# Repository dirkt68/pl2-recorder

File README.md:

#Automated Recorder Project
##Texas Tech University PL2

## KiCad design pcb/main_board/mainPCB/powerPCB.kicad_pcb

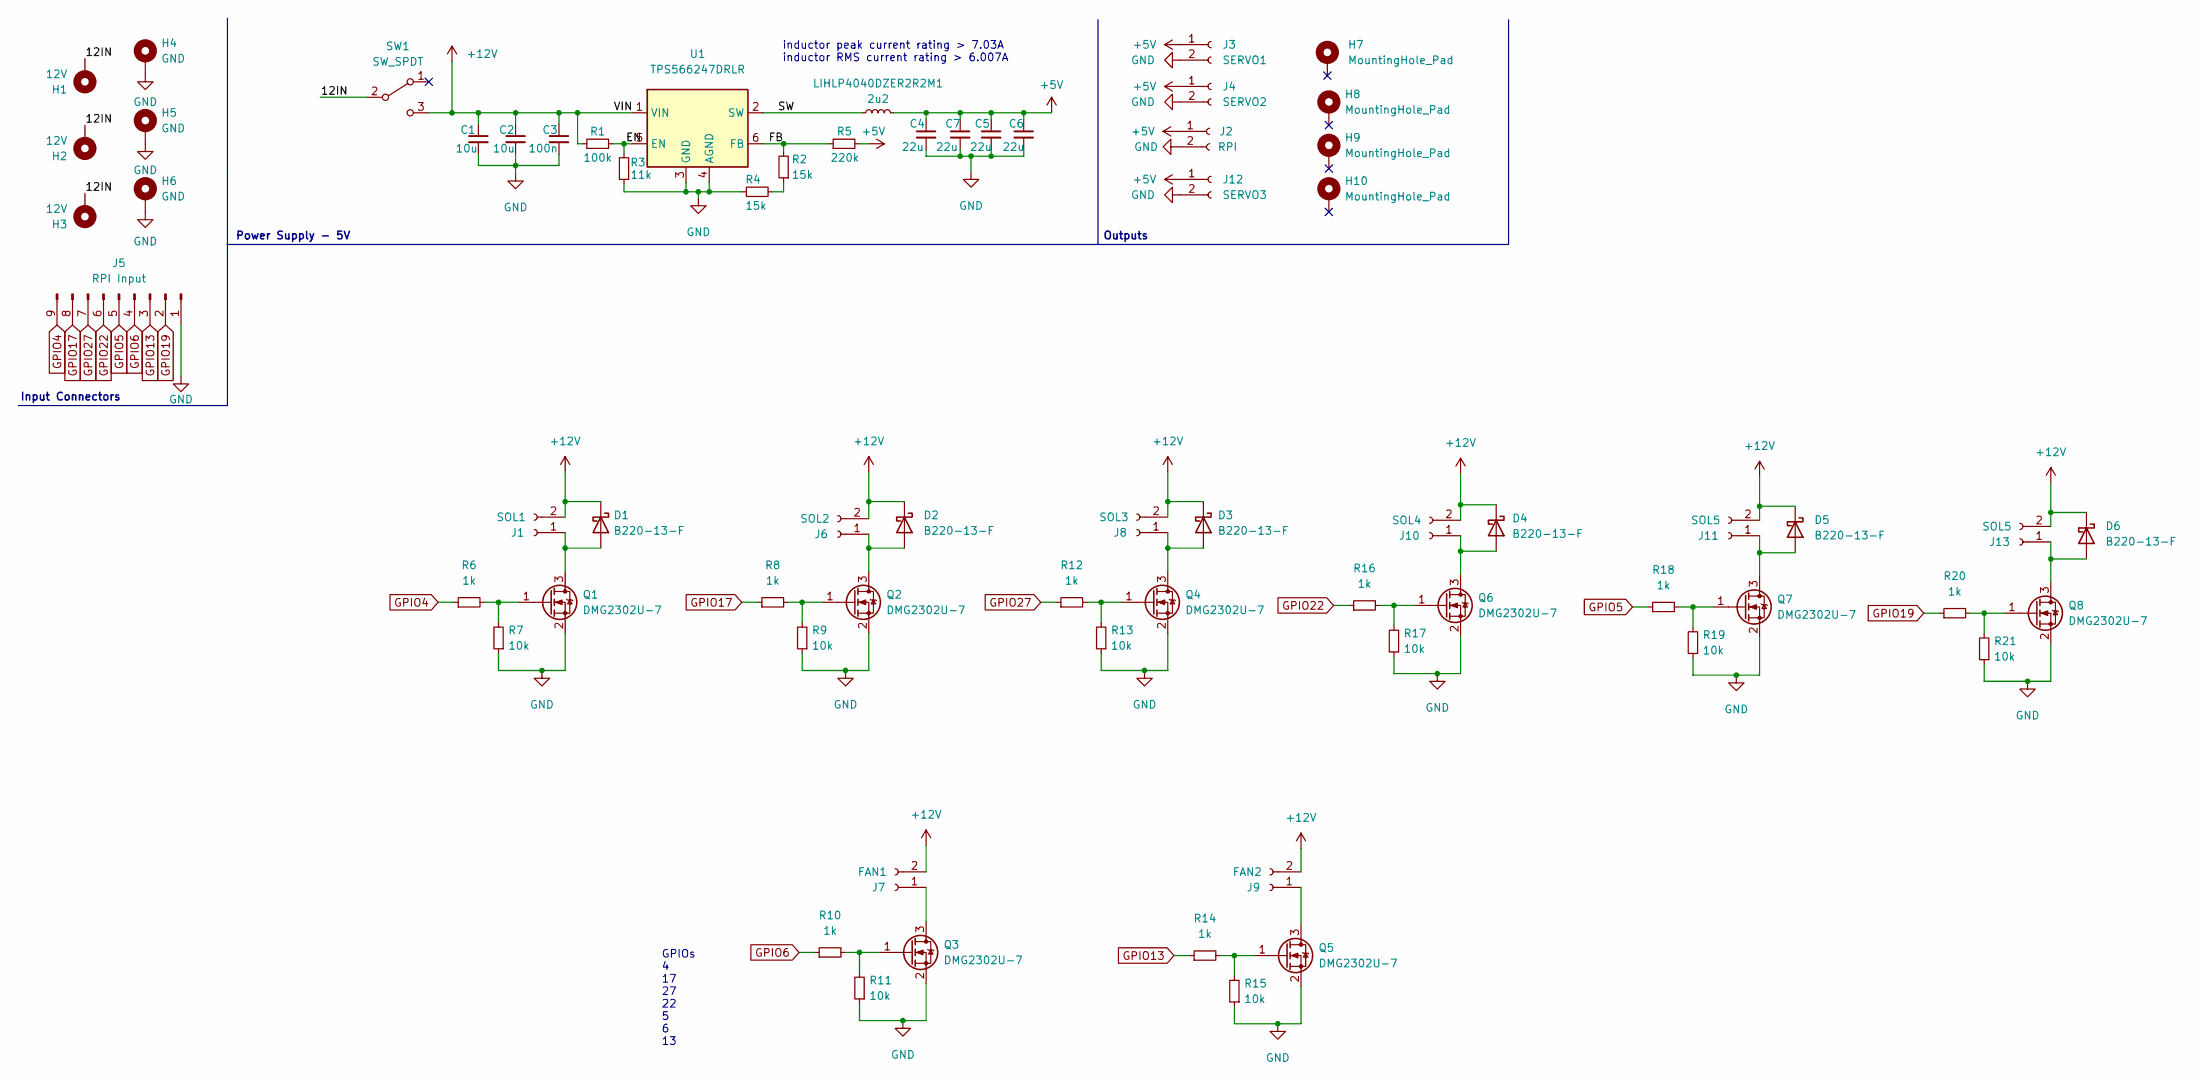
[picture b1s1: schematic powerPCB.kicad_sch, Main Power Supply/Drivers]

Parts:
C1, C2: 10u; C_1206_3216Metric
C3: 100n; C_0603_1608Metric
C4, C5, C6, C7: 22u; C_1210_3225Metric
D1, D2, D3, D4, D5, D6: B220-13-F; D_SMB
H1, H2, H3: 12V; MountingHole_2.2mm_M2_DIN965_Pad
H4, H5, H6: GND; MountingHole_2.2mm_M2_DIN965_Pad
H7, H8, H9, H10: MountingHole_Pad; MountingHole_3.2mm_M3_DIN965_Pad
J1: SOL1; PinHeader_1x02_P5.00mm
J2: RPI; PinHeader_1x02_P5.00mm
J3: SERVO1; PinHeader_1x02_P5.00mm
J4: SERVO2; PinHeader_1x02_P5.00mm
J5: RPI Input; PinHeader_1x09_P2.54mm_Vertical
J6: SOL2; PinHeader_1x02_P5.00mm
J7: FAN1; PinHeader_1x02_P5.00mm
J8: SOL3; PinHeader_1x02_P5.00mm
J9: FAN2; PinHeader_1x02_P5.00mm
J10: SOL4; PinHeader_1x02_P5.00mm
J11, J13: SOL5; PinHeader_1x02_P5.00mm
J12: SERVO3; PinHeader_1x02_P5.00mm
LIHLP4040DZER2R2M1: 2u2; L_Vishay_IHLP-4040
Q1, Q2, Q3, Q4, Q5, Q6, Q7, Q8: DMG2302U-7; SOT-23
R1: 100k; R_0603_1608Metric
R2, R4: 15k; R_0603_1608Metric
R3: 11k; R_0603_1608Metric
R5: 220k; R_1206_3216Metric
R6, R8, R10, R12, R14, R16, R18, R20: 1k; R_0805_2012Metric
R7, R9, R11, R13, R15, R17, R19, R21: 10k; R_0805_2012Metric
SW1: SW_SPDT; remote switch
U1: TPS566247DRLR; SOT-563

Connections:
+5V: C4.1, C5.1, C6.1, C7.1, J2.1, J3.1, J4.1, J12.1, LIHLP4040DZER2R2M1.2, R5.2
+12V: C1.1, C2.1, C3.1, D1.1 (K), D2.1 (K), D3.1 (K), D4.1 (K), D5.1 (K), D6.1 (K), J1.2, J6.2, J7.2, J8.2, J9.2, J10.2, J11.2, J13.2, R1.1, SW1.3 (C), U1.1 (VIN)
/12IN: H1.1, H2.1, H3.1, SW1.2 (B)
/EN: R1.2, R3.2, U1.5 (EN)
/FB: R2.2, R5.1, U1.6 (FB)
/SW: LIHLP4040DZER2R2M1.1, U1.2 (SW)
GND: C1.2, C2.2, C3.2, C4.2, C5.2, C6.2, C7.2, H4.1, H5.1, H6.1, J2.2, J3.2, J4.2, J5.1, J12.2, Q1.2 (S), Q2.2 (S), Q3.2 (S), Q4.2 (S), Q5.2 (S), Q6.2 (S), Q7.2 (S), Q8.2 (S), R3.1, R4.1, R7.1, R9.1, R11.1, R13.1, R15.1, R17.1, R19.1, R21.1, U1.3 (GND), U1.4 (AGND)
GPIO4: J5.9, R6.1
GPIO5: J5.5, R18.1
GPIO6: J5.4, R10.1
GPIO13: J5.3, R14.1
GPIO17: J5.8, R8.1
GPIO19: J5.2, R20.1
GPIO22: J5.6, R16.1
GPIO27: J5.7, R12.1
unnamed: D1.2 (A), J1.1, Q1.3 (D)
unnamed: D2.2 (A), J6.1, Q2.3 (D)
unnamed: D3.2 (A), J8.1, Q4.3 (D)
unnamed: D5.2 (A), J11.1, Q7.3 (D)
unnamed: D6.2 (A), J13.1, Q8.3 (D)
unnamed: J7.1, Q3.3 (D)
unnamed: J9.1, Q5.3 (D)
unnamed: Q1.1 (G), R6.2, R7.2
unnamed: Q2.1 (G), R8.2, R9.2
unnamed: Q3.1 (G), R10.2, R11.2
unnamed: Q4.1 (G), R12.2, R13.2
unnamed: Q5.1 (G), R14.2, R15.2
unnamed: Q6.1 (G), R16.2, R17.2
unnamed: D4.2 (A), J10.1, Q6.3 (D)
unnamed: Q7.1 (G), R18.2, R19.2
unnamed: Q8.1 (G), R20.2, R21.2
unnamed: R2.1, R4.2

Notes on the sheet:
Power Supply - 5V
Input Connectors
Outputs
inductor peak current rating > 7.03A inductor RMS current rating > 6.007A
GPIOs 4 17 27 22 5 6 13

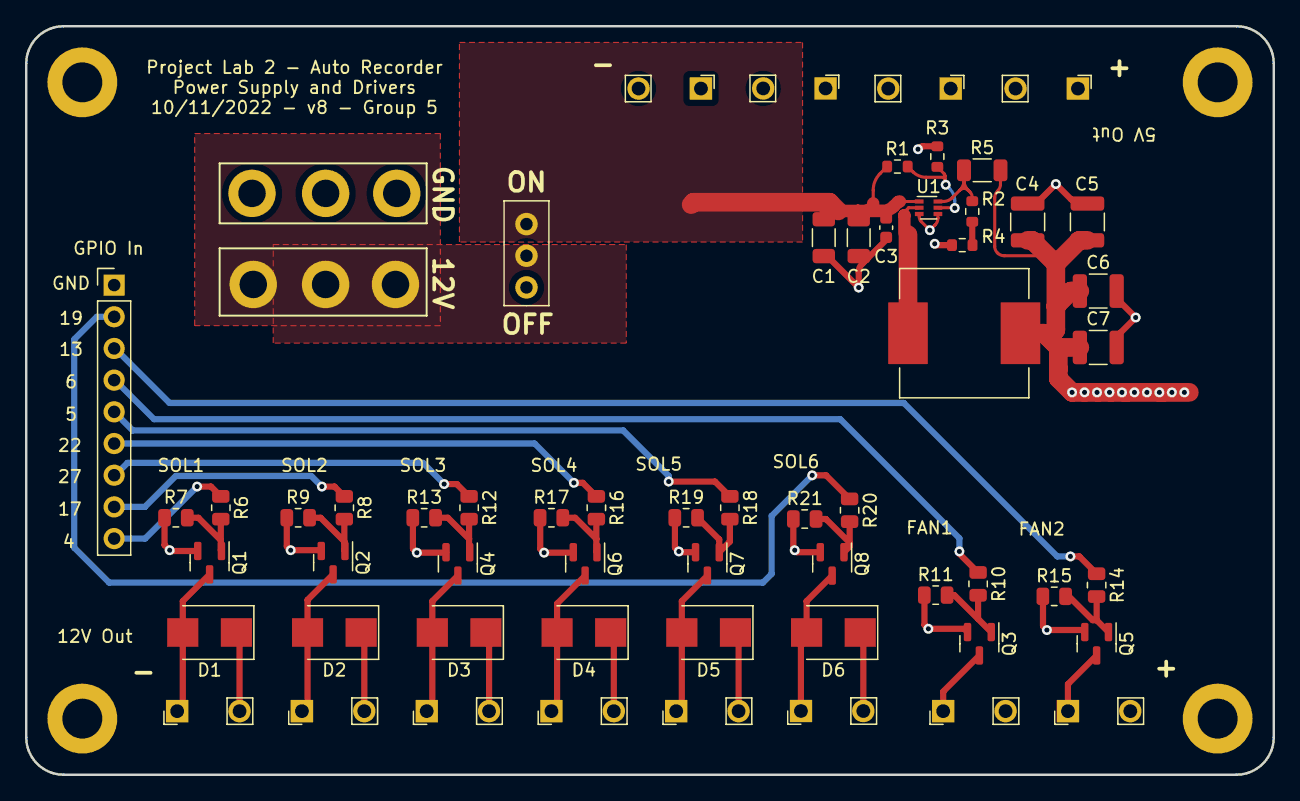
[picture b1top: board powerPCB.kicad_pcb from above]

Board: 4 copper layers, 100.0 x 60.0 mm, 68 parts (0 on the bottom side), 32 nets.

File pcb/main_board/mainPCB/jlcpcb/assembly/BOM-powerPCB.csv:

Comment,Designator,Footprint,LCSC
100k,R1,R_0603_1608Metric,
GND,H5,MountingHole_2.2mm_M2_DIN965_Pad,
22u,C5,C_1210_3225Metric,
SOL4,J10,PinHeader_1x02_P5.00mm,
SERVO1,J3,PinHeader_1x02_P5.00mm,
11k,R3,R_0603_1608Metric,
15k,R2,R_0603_1608Metric,
FAN1,J7,PinHeader_1x02_P5.00mm,
10u,C2,C_1206_3216Metric,
SOL2,J6,PinHeader_1x02_P5.00mm,
FAN2,J9,PinHeader_1x02_P5.00mm,
GND,H6,MountingHole_2.2mm_M2_DIN965_Pad,
SERVO2,J4,PinHeader_1x02_P5.00mm,
SOL3,J8,PinHeader_1x02_P5.00mm,
22u,C4,C_1210_3225Metric,
12V,H2,MountingHole_2.2mm_M2_DIN965_Pad,
100n,C3,C_0603_1608Metric,
SOL1,J1,PinHeader_1x02_P5.00mm,
12V,H3,MountingHole_2.2mm_M2_DIN965_Pad,
RPI Input,J5,PinHeader_1x09_P2.54mm_Vertical,
12V,H1,MountingHole_2.2mm_M2_DIN965_Pad,
SW_SPDT,SW1,remote switch,
10u,C1,C_1206_3216Metric,
TPS566247DRLR,U1,SOT-563,
22u,C6,C_1210_3225Metric,
220k,R5,R_1206_3216Metric,
GND,H4,MountingHole_2.2mm_M2_DIN965_Pad,
22u,C7,C_1210_3225Metric,
RPI,J2,PinHeader_1x02_P5.00mm,
15k,R4,R_0603_1608Metric,
SOL5,J11,PinHeader_1x02_P5.00mm,
10k,R19,R_0805_2012Metric,
1k,R18,R_0805_2012Metric,
10k,R17,R_0805_2012Metric,
1k,R16,R_0805_2012Metric,
10k,R15,R_0805_2012Metric,
1k,R14,R_0805_2012Metric,
10k,R13,R_0805_2012Metric,
1k,R12,R_0805_2012Metric,
10k,R11,R_0805_2012Metric,
1k,R10,R_0805_2012Metric,
10k,R9,R_0805_2012Metric,
1k,R8,R_0805_2012Metric,
10k,R7,R_0805_2012Metric,
1k,R6,R_0805_2012Metric,
DMG2302U-7,Q7,SOT-23,
DMG2302U-7,Q6,SOT-23,
DMG2302U-7,Q5,SOT-23,
DMG2302U-7,Q4,SOT-23,
DMG2302U-7,Q3,SOT-23,
DMG2302U-7,Q2,SOT-23,
DMG2302U-7,Q1,SOT-23,
B220-13-F,D5,D_SMB,
B220-13-F,D4,D_SMB,
B220-13-F,D3,D_SMB,
B220-13-F,D2,D_SMB,
B220-13-F,D1,D_SMB,
MountingHole_Pad,H9,MountingHole_3.2mm_M3_DIN965_Pad,
MountingHole_Pad,H10,MountingHole_3.2mm_M3_DIN965_Pad,
MountingHole_Pad,H8,MountingHole_3.2mm_M3_DIN965_Pad,
MountingHole_Pad,H7,MountingHole_3.2mm_M3_DIN965_Pad,
DMG2302U-7,Q8,SOT-23,
1k,R20,R_0805_2012Metric,
10k,R21,R_0805_2012Metric,
SOL5,J13,PinHeader_1x02_P5.00mm,
B220-13-F,D6,D_SMB,
2u2,LIHLP4040DZER2R2M1,L_Vishay_IHLP-4040,
SERVO3,J12,PinHeader_1x02_P5.00mm,

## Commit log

2022-09-20 first upload, most of code finished
2022-10-03 updated folders
2022-10-24 updated code, half of report, and PCB
2022-10-25 finished report
2022-11-15 added more code
2022-11-21 more code
2022-11-28 code
2022-11-29 added some code
2022-12-03 transfer
2022-12-07 more transfer
2022-12-07 comments
